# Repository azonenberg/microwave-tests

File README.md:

# microwave-tests
RF/microwave test boards that didn't fit anywhere else

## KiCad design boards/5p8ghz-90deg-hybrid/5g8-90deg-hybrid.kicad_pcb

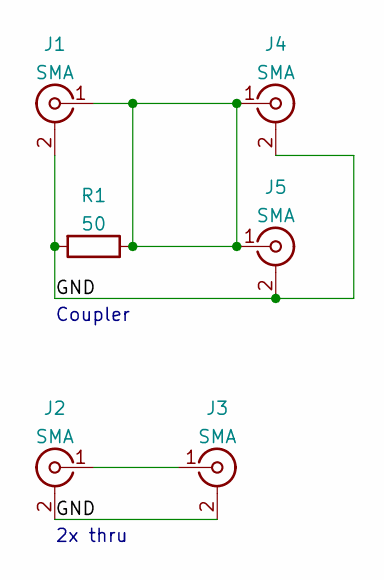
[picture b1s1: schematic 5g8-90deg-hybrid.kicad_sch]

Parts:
J1, J2, J3, J4, J5: SMA; CONN_SMA_EDGE_SAMTEC_SMA_J_P_H_ST_EM1
R1: 50; EIA_0402_RES_NOSILK_FLIPCHIP

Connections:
/GND: J1.2 (Ext), J2.2 (Ext), J3.2 (Ext), J4.2 (Ext), J5.2 (Ext), R1.2
unnamed: J1.1 (In), J4.1 (In), J5.1 (In), R1.1
unnamed: J2.1 (In), J3.1 (In)

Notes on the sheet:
Coupler
2x thru

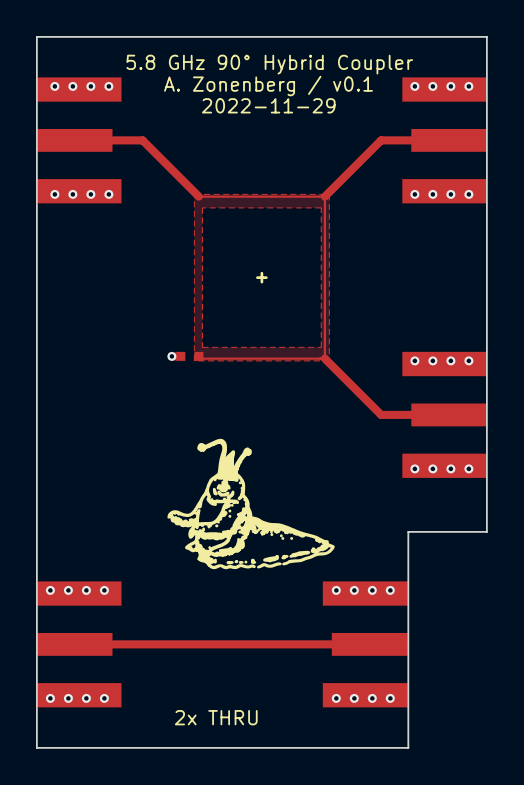
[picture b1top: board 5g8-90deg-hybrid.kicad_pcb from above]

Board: 4 copper layers, 25.0 x 39.5 mm, 6 parts (0 on the bottom side), 3 nets.

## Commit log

2022-11-29 Initial version of 5.8 GHz 90 degree hybrid
2022-11-30 Continued work on 90-deg hybrid model
